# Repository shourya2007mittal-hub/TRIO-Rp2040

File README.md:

# TRIO-Rp2040

So I made on a Dev-board based on Rp-2040 with similar size constrain like Xiao-Rp2040 but with more available pins then Xiao. So I used the smallest size of resistors and capacitors . It has access to a total of 21 GPI0 and 4 Analog . 6 Pins act as dual purpose. It holds an USB-C Type interference for communication and 3.3V Voltage regulator and Crystal oscillator , Flash Memory , boot Switch  and more 

## Features

- Based on RP-2040 Chip
- Has MCP1700x-330xxTT as Voltage Regulator 
- Has W25Q16JVUXIQTR as Flash Memory
- Has 3 set of 7 connector pins  
- Has 2 set of 2 connector pins for GND and 3.3V
- It is compatible to a breadboard 

## Cost Summary (BOM)

| Item | Quantity | Price (USD) | Source |
|------|------------|------------|---------|
| PCB + PCBA + Shipping  | 1 | $81.91 | JLCPCB |

**Total Estimated Cost:** **$81.91**

### Schematic

### PCB Design

### 3D Design

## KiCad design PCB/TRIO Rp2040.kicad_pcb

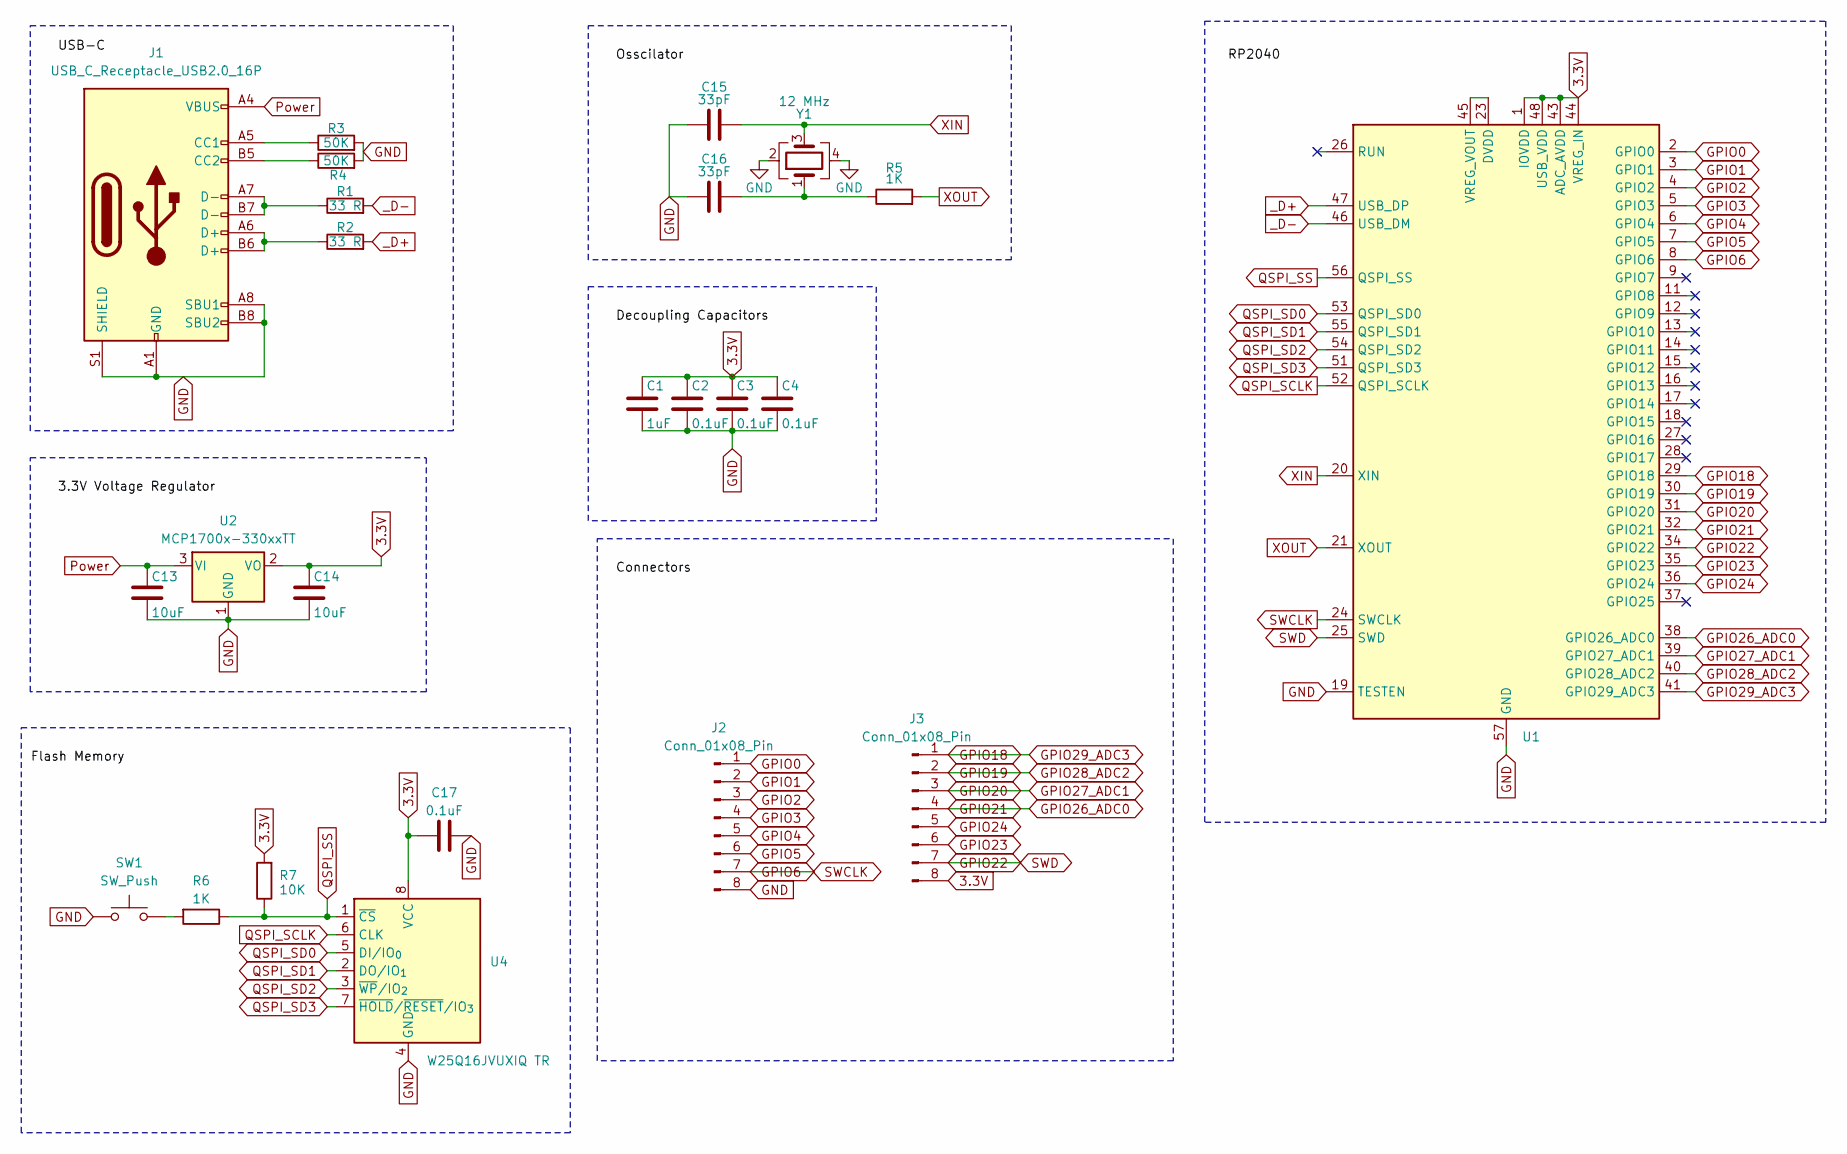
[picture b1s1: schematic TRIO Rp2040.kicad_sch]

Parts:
C1: 1uF; C_0201_0603Metric
C2, C3, C4, C17: 0.1uF; C_0201_0603Metric
C13, C14: 10uF; C_0201_0603Metric
C15, C16: 33pF; C_0201_0603Metric
J1: USB_C_Receptacle_USB2.0_16P; USB_C_Receptacle_G-Switch_GT-USB-7010ASV
J2, J3: Conn_01x08_Pin; Molex_SL_171971-0008_1x08_P2.54mm_Vertical
R1, R2: 33 R; R_0201_0603Metric
R3, R4: 50K; R_0201_0603Metric
R5, R6: 1K; R_0201_0603Metric
R7: 10K; R_0201_0603Metric
SW1: SW_Push; SW_Push_SPST_NO_Alps_SKRK
U1: RP2040; QFN-56-1EP_7x7mm_P0.4mm_EP3.2x3.2mm
U2: MCP1700x-330xxTT; SOT-23
U4: W25Q16JVUXIQ TR; Winbond_USON-8-1EP_3x2mm_P0.5mm_EP0.2x1.6mm
Y1: 12 MHz; Crystal_SMD_1210-4Pin_1.2x1.0mm

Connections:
3.3V: C1.1, C2.1, C3.1, C4.1, C14.1, C17.1, J3.8, R7.2, U1.1 (IOVDD), U1.10 (IOVDD), U1.22 (IOVDD), U1.33 (IOVDD), U1.42 (IOVDD), U1.43 (ADC_AVDD), U1.44 (VREG_IN), U1.48 (USB_VDD), U1.49 (IOVDD), U2.2 (VO), U4.8 (VCC)
GND: C1.2, C2.2, C3.2, C4.2, C13.2, C14.2, C15.1, C16.1, C17.2, J1.A1 (GND), J1.A8 (SBU1), J1.A12 (GND), J1.B1 (GND), J1.B8 (SBU2), J1.B12 (GND), J1.S1 (SHIELD), J2.8, R3.2, R4.2, SW1.1, U1.19 (TESTEN), U1.57 (GND), U2.1 (GND), U4.4 (GND), Y1.2, Y1.4
GPIO0: J2.1, U1.2 (GPIO0)
GPIO1: J2.2, U1.3 (GPIO1)
GPIO2: J2.3, U1.4 (GPIO2)
GPIO3: J2.4, U1.5 (GPIO3)
GPIO4: J2.5, U1.6 (GPIO4)
GPIO5: J2.6, U1.7 (GPIO5)
GPIO6: J2.7, U1.8 (GPIO6), U1.24 (SWCLK)
GPIO18: J3.1, U1.29 (GPIO18), U1.41 (GPIO29_ADC3)
GPIO19: J3.2, U1.30 (GPIO19), U1.40 (GPIO28_ADC2)
GPIO20: J3.3, U1.31 (GPIO20), U1.39 (GPIO27_ADC1)
GPIO21: J3.4, U1.32 (GPIO21), U1.38 (GPIO26_ADC0)
GPIO22: J3.7, U1.25 (SWD), U1.34 (GPIO22)
GPIO23: J3.6, U1.35 (GPIO23)
GPIO24: J3.5, U1.36 (GPIO24)
unnamed: C16.2, R5.1, Y1.1
unnamed: J1.A5 (CC1), R3.1
unnamed: J1.B5 (CC2), R4.1
unnamed: J1.A6 (D+), J1.B6 (D+), R2.1
unnamed: J1.A7 (D-), J1.B7 (D-), R1.1
unnamed: R6.2, SW1.2
unnamed: U1.23 (DVDD), U1.45 (VREG_VOUT), U1.50 (DVDD)
Power: C13.1, J1.A4 (VBUS), J1.A9 (VBUS), J1.B4 (VBUS), J1.B9 (VBUS), U2.3 (VI)
QSPI_SCLK: U1.52 (QSPI_SCLK), U4.6 (CLK)
QSPI_SD0: U1.53 (QSPI_SD0), U4.5 (DI/IO_{0})
QSPI_SD1: U1.55 (QSPI_SD1), U4.2 (DO/IO_{1})
QSPI_SD2: U1.54 (QSPI_SD2), U4.3 (~WP/IO_{2})
QSPI_SD3: U1.51 (QSPI_SD3), U4.7 (~HOLD/~RESET/IO_{3})
QSPI_SS: R6.1, R7.1, U1.56 (QSPI_SS), U4.1 (~CS)
XIN: C15.2, U1.20 (XIN), Y1.3
XOUT: R5.2, U1.21 (XOUT)
_D+: R2.2, U1.47 (USB_DP)
_D-: R1.2, U1.46 (USB_DM)

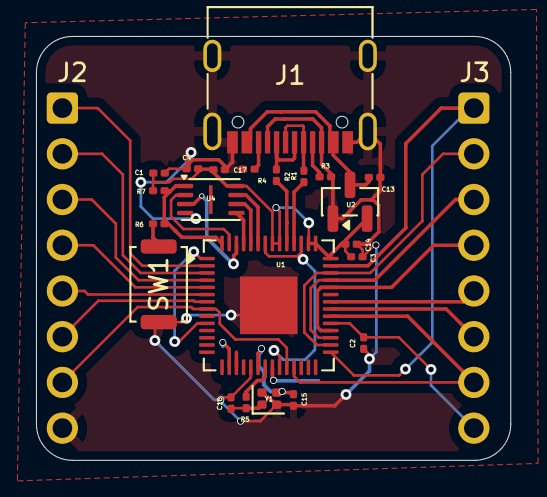
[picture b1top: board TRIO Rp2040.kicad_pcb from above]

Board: 2 copper layers, 26.4 x 23.5 mm, 24 parts (0 on the bottom side), 34 nets.

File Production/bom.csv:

Designator,Footprint,Quantity,Value,LCSC Part #
C1,0201,1,1uF,
"C13, C14",0201,2,10uF,
"C15, C16",0201,2,33pF,
"C17, C2, C3, C4",0201,4,0.1uF,
J1,USB_C_Receptacle_G-Switch_GT-USB-7010ASV,1,USB_C_Receptacle_USB2.0_16P,
"J2, J3",Hirose_DF13-02P-1.25DSA_1x02_P1.25mm_Vertical,2,Conn_01x02_Pin,
"J5, J6, J7",Hirose_DF13-07P-1.25DSA_1x07_P1.25mm_Vertical,3,Conn_01x07_Pin,
"R1, R2",0201,2,33 R,
"R3, R4",0201,2,50K,
"R5, R6",0201,2,1K,
R7,0201,1,10K,
SW1,SW_Push_SPST_NO_Alps_SKRK,1,SW_Push,
U1,QFN-56-1EP_7x7mm_P0.4mm_EP3.2x3.2mm,1,RP2040,
U2,SOT-23,1,MCP1700x-330xxTT,
U4,Winbond_USON-8-1EP_3x2mm_P0.5mm_EP0.2x1.6mm,1,W25Q16JVUXIQ TR,
Y1,Crystal_SMD_1210-4Pin_1.2x1.0mm,1,12 MHz,
